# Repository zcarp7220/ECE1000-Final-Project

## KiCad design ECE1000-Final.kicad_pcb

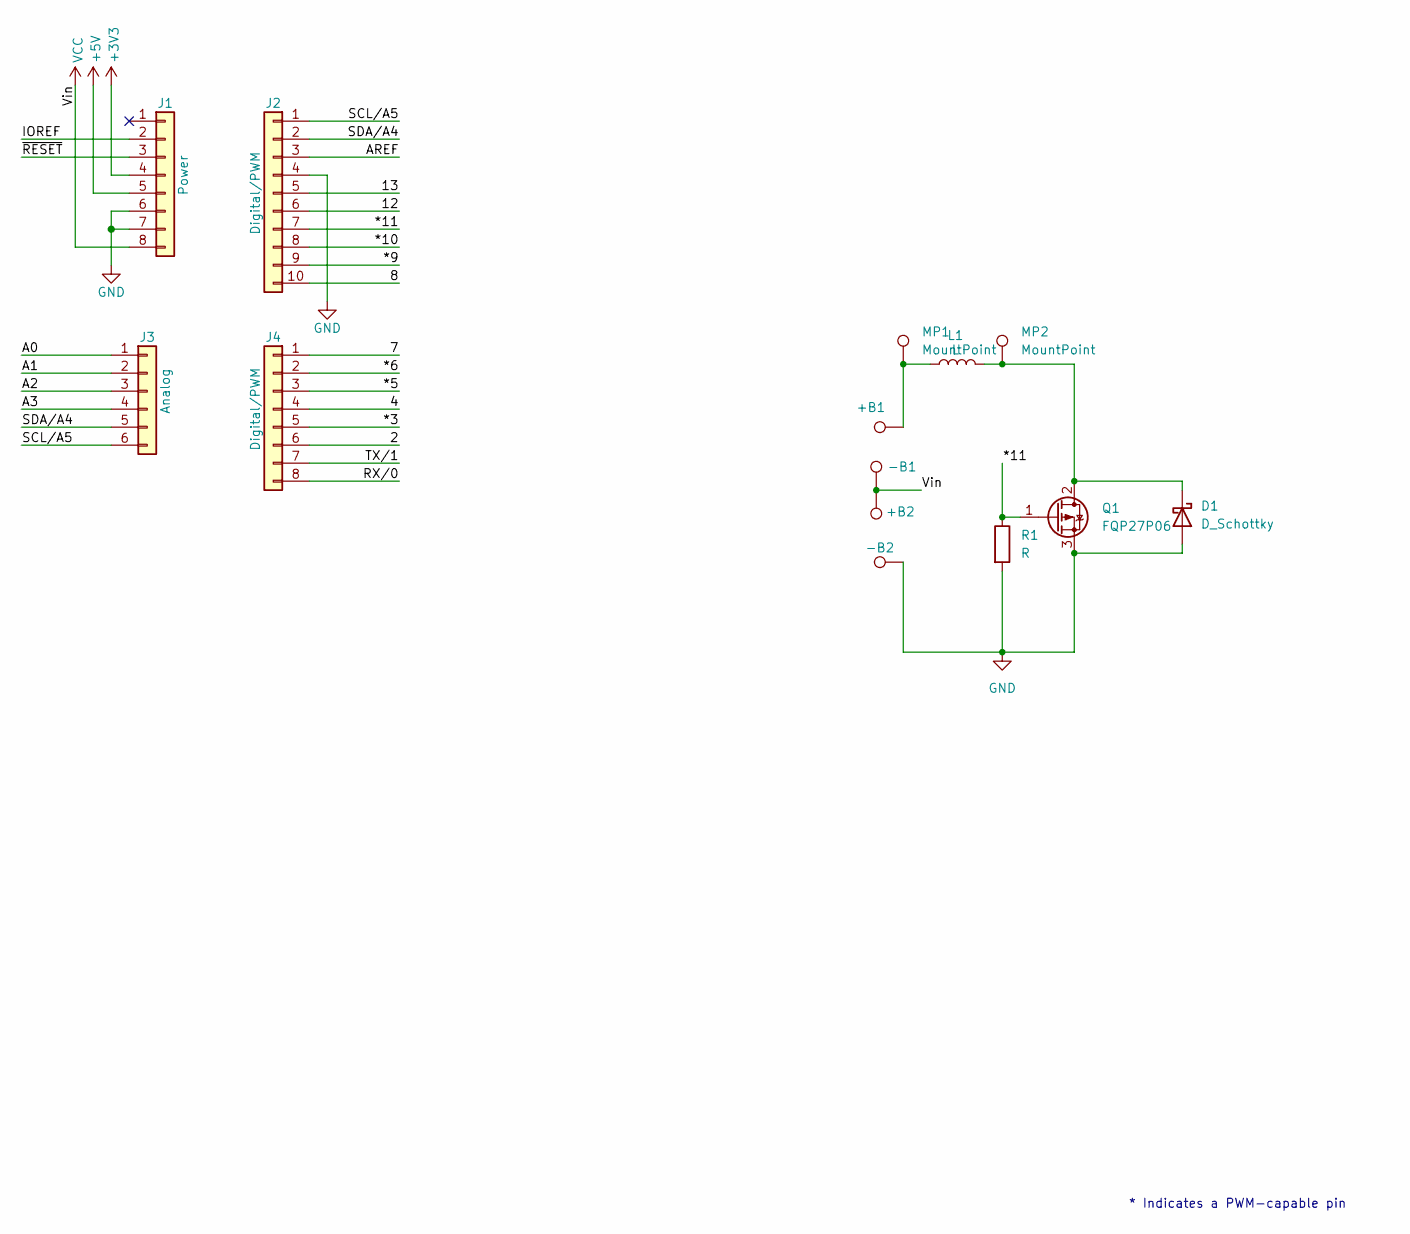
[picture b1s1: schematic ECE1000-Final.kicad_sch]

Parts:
+B1, +B2: TestPoint; AAAABatteryConnection
-B1, -B2: TestPoint; AAAABatteryConnection
D1: D_Schottky; D_DO-27_P5.08mm_Vertical_CathodeUp
J1: Power; PinSocket_1x08_P2.54mm_Vertical
J2: Digital/PWM; PinSocket_1x10_P2.54mm_Vertical
J3: Analog; PinSocket_1x06_P2.54mm_Vertical
J4: Digital/PWM; PinSocket_1x08_P2.54mm_Vertical
L1: L; THEULTCOIL
MP1: MountPoint; TestPoint_THTPad_D1.0mm_Drill0.5mm
MP2: MountPoint; TestPoint_THTPad_1.0x1.0mm_Drill0.5mm
Q1: FQP27P06; TO-220-3_Vertical
R1: R; R_Axial_DIN0207_L6.3mm_D2.5mm_P10.16mm_Horizontal

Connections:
+3V3: J1.4
+5V: J1.5
/2: J4.6
/4: J4.4
/7: J4.1
/8: J2.10
/12: J2.6
/13: J2.5
/*3: J4.5
/*5: J4.3
/*6: J4.2
/*9: J2.9
/*10: J2.8
/*11: J2.7, Q1.1 (G), R1.1
/A0: J3.1
/A1: J3.2
/A2: J3.3
/A3: J3.4
/AREF: J2.3
/IOREF: J1.2
/RX/0: J4.8
/SCL/A5: J2.1, J3.6
/SDA/A4: J2.2, J3.5
/TX/1: J4.7
/~RESET: J1.3
GND: -B2.1 (1_1), D1.2 (A), J1.6, J1.7, J2.4, Q1.3 (S), R1.2
unnamed: +B1.1 (1_1), L1.1, MP1.1 (1_1)
unnamed: D1.1 (K), L1.2, MP2.1 (1_1), Q1.2 (D)
VCC: +B2.1 (1_1), -B1.1 (1_1), J1.8

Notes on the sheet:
* Indicates a PWM-capable pin

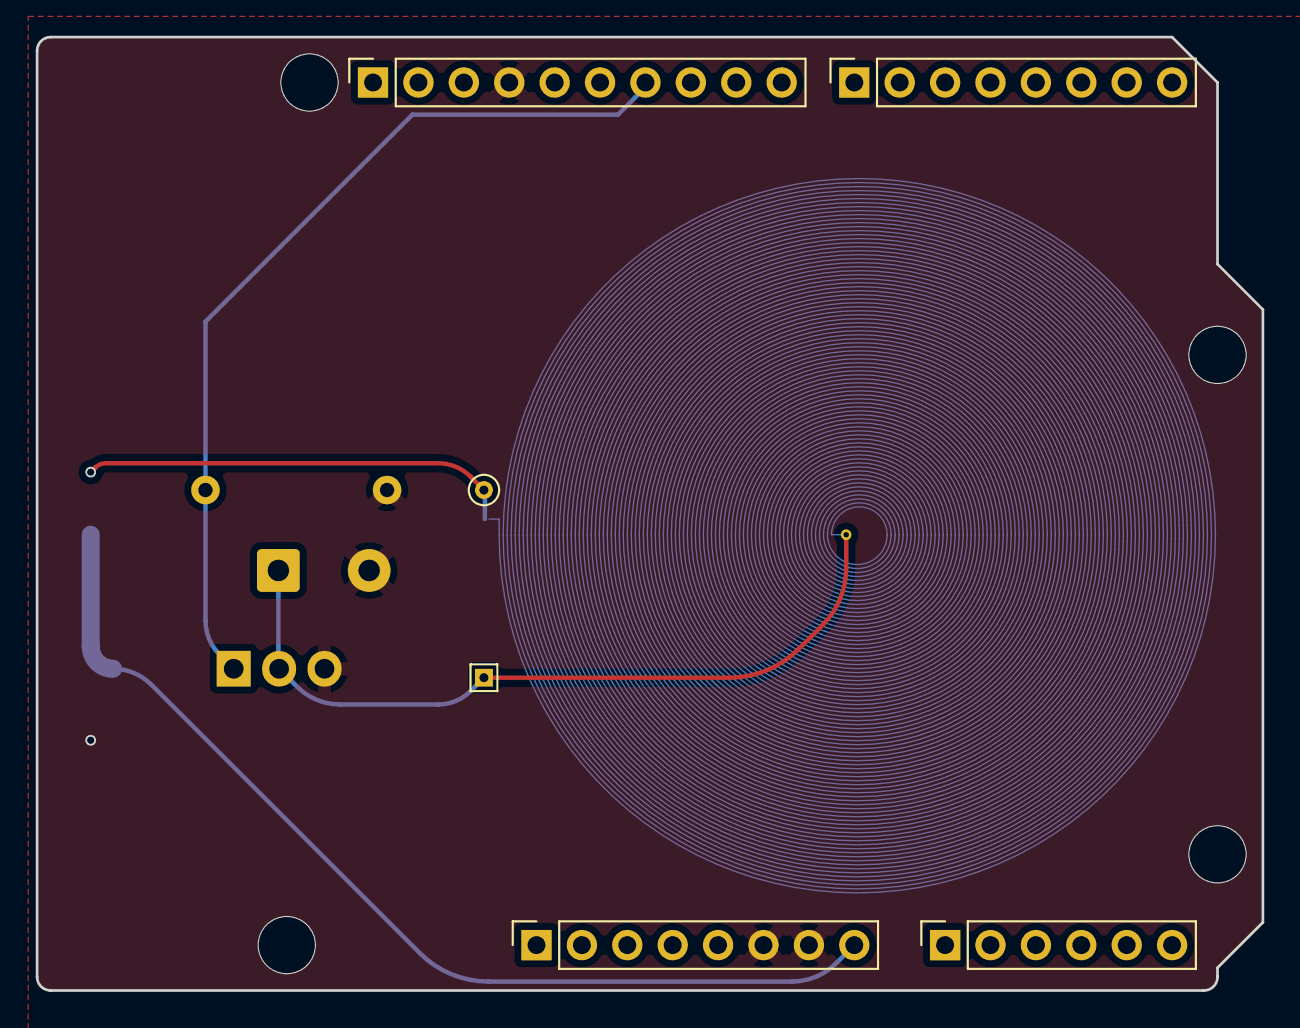
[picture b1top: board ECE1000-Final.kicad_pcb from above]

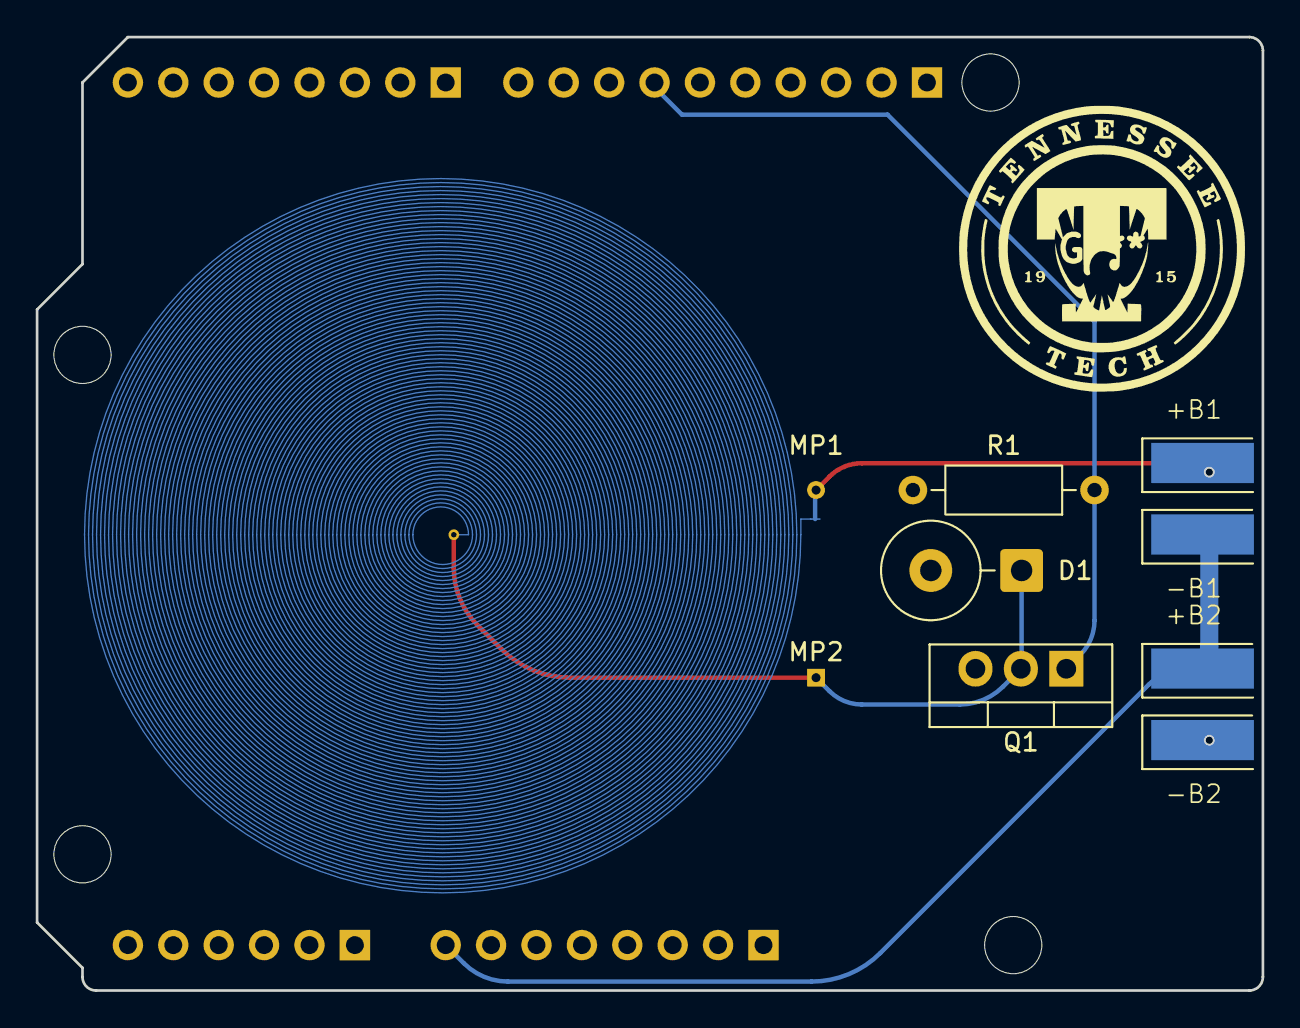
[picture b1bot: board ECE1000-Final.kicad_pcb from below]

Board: 2 copper layers, 68.6 x 53.3 mm, 18 parts (8 on the bottom side), 7 nets.

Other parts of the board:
MH1, MH2, MH3, MH4: MountingHole_3.2mm
